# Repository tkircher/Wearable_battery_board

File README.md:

# Wearable_battery_board
This is the battery management board for the wearable

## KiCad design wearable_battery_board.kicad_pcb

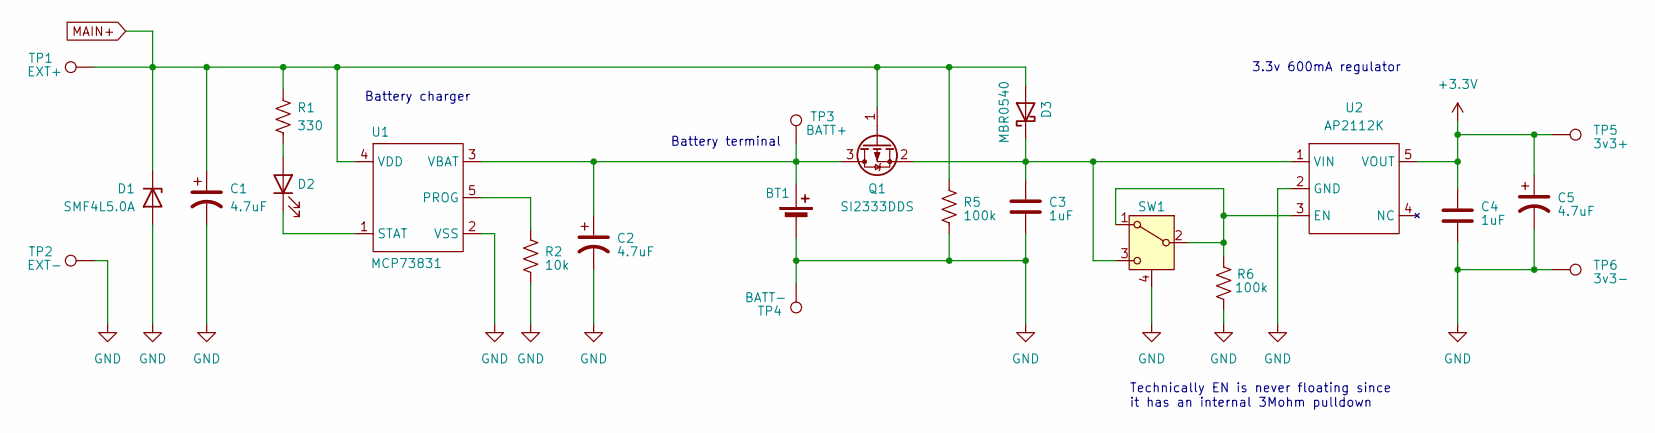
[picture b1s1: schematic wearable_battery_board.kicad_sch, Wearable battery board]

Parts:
BT1: Battery_Cell
C1, C2, C5: 4.7uF; CP_EIA-2012-15_AVX-P
C3, C4: 1uF; C_0603_1608Metric
D1: SMF4L5.0A; D_SOD-123F
D2: LED; LED_0603_1608Metric
D3: MBR0540; D_SOD-123
Q1: SI2333DDS; SOT-23-3
R1: 330; R_0603_1608Metric
R2: 10k; R_0603_1608Metric
R5, R6: 100k; R_0603_1608Metric
SW1: SW_SPDT; CUS-12TB_NDC
TP1: EXT+; TestPoint_Pad_2.0x2.0mm
TP2: EXT-; TestPoint_Pad_2.0x2.0mm
TP3: BATT+; TestPoint_Pad_2.0x2.0mm
TP4: BATT-; TestPoint_Pad_2.0x2.0mm
TP5: 3v3+; TestPoint_Pad_2.0x2.0mm
TP6: 3v3-; TestPoint_Pad_2.0x2.0mm
U1: MCP73831; SOT-23-5
U2: AP2112K; SOT-23-5

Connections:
+3.3V: C4.1, C5.1, TP5.1, U2.5 (VOUT)
GND: BT1.2 (-), C1.2, C2.2, C3.2, C4.2, C5.2, D1.2 (A), R2.2, R5.2, R6.1, SW1.4 (GND), TP2.1, TP4.1, TP6.1, U1.2 (VSS), U2.2 (GND)
MAIN+: C1.1, D1.1 (K), D3.2 (A), Q1.1 (G), R1.1, R5.1, TP1.1, U1.4 (VDD)
unnamed: D2.2 (A), R1.2
unnamed: D2.1 (K), U1.1 (STAT)
unnamed: C3.1, D3.1 (K), Q1.2 (S), SW1.3 (C), U2.1 (VIN)
unnamed: BT1.1 (+), C2.1, Q1.3 (D), TP3.1, U1.3 (VBAT)
unnamed: R6.2, SW1.1 (A), SW1.2 (B), U2.3 (EN)
unnamed: R2.1, U1.5 (PROG)

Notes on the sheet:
Technically EN is never floating since it has an internal 3Mohm pulldown
Battery charger
3.3v 600mA regulator
Battery terminal

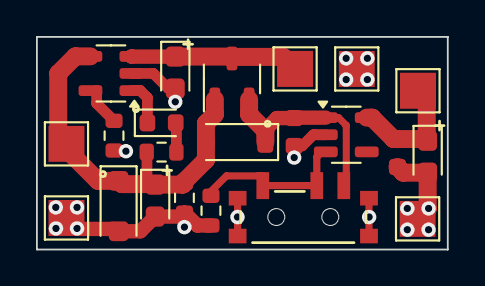
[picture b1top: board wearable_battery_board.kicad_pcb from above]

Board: 2 copper layers, 22.8 x 11.8 mm, 22 parts (0 on the bottom side), 9 nets.

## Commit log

2025-01-11 Create LICENSE
